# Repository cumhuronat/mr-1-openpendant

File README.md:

# mr-1-openpendant
An opensource pendant project for MR-1 CNC

## Overview
This project implements an open-source pendant system for the MR-1 CNC machine, providing a user-friendly interface for machine control and monitoring.
The system consists of two main components and detailed documentation for them can be found within their respective submodules.

### Pendant
- Custom-designed handheld controller
- Features a display interface for machine status and control
- Built using ESP32-based hardware
- Includes software implementation for the user interface and control logic

### Dongle
- USB interface for CNC machine communication
- Components:
  - PCB design files
  - 3D-printable enclosure
  - Arduino-based firmware using TinyUSB
  - Interface software

## Project Structure
- `/pendant` - Main pendant implementation
  - `/software` - Pendant firmware and interface code
- `/dongle` - USB interface dongle
  - `/enclosure` - 3D design files for the dongle case
  - `/pcb` - PCB design files
  - `/software` - Interface software

## Development Status
This project is currently under active development as part of the IMGD 5100 course final project.

## Acknowledgments
Special thanks to [Charlie Roberts](https://github.com/charlieroberts) for allowing this project to be developed as part of the IMGD 5100 final project.

## License
This project is open source and available under the[MIT License](https://opensource.org/licenses/MIT).

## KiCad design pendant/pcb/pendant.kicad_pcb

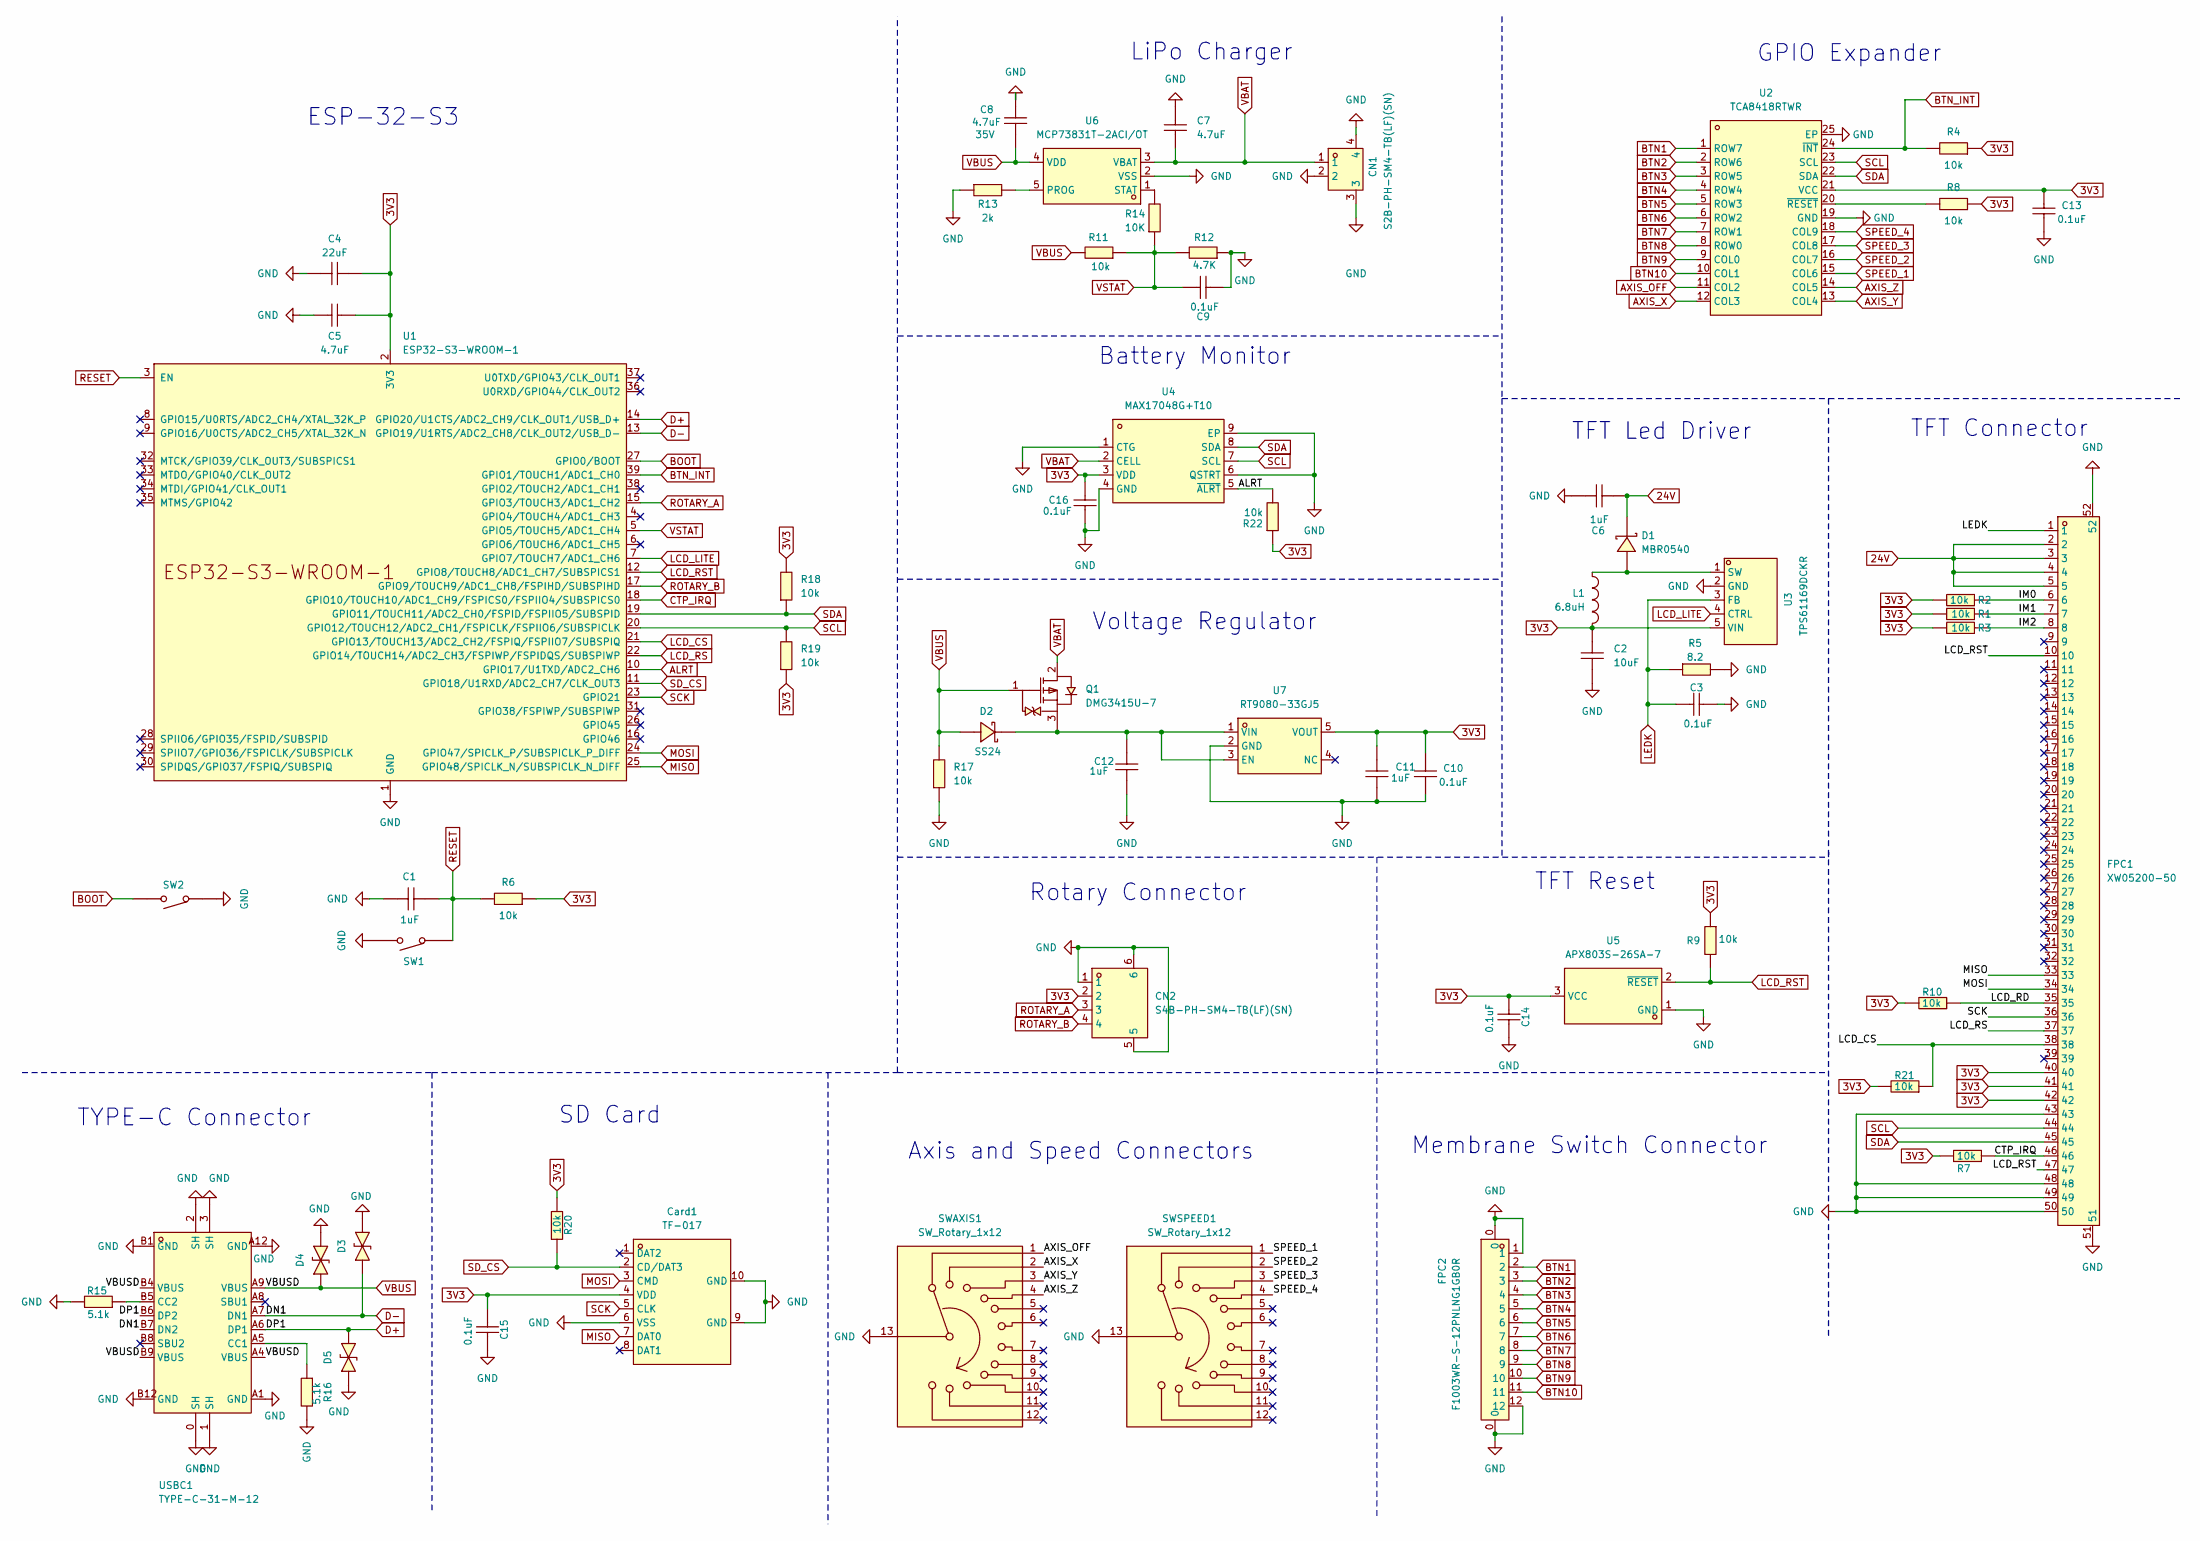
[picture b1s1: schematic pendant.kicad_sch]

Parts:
C1, C6, C11, C12: 1uF; C0402; LCSC Part C52923
C2: 10uF; C0805; LCSC Part C15850
C3, C9, C10, C13, C14, C15, C16: 0.1uF; C0402; LCSC Part C1525
C4: 22uF; C0603; LCSC Part C59461
C5, C7: 4.7uF; C0402; LCSC Part C23733
C8: 4.7uF; C0805; Voltage 35V; LCSC Part C668361
CN1: S2B-PH-SM4-TB(LF)(SN); CONN-SMD_P2.00_S2B-PH-SM4-TB-LF-SN; LCSC Part C295747
CN2: S4B-PH-SM4-TB(LF)(SN); CONN-SMD_S4B-PH-SM4-TB-LF-SN; LCSC Part C265102
Card1: TF-017; TF-SMD_TF-017; LCSC Part C410348
D1: MBR0540; SOD-123FL_L2.7-W1.8-LS3.8-RD; LCSC Part C116159
D2: SS24; SMA_L4.4-W2.8-LS5.4-R-RD; LCSC Part C489139
D3, D4, D5: LESD5D5.0CT1G; SOD-523_L1.2-W0.8-LS1.6-BI; LCSC Part C5246195
FPC1: XW05200-50; FPC-SMD_50P-P0.50_XW05200-50; LCSC Part C376073
FPC2: F1003WR-S-12PNLNG1GB0R; FPC-SMD_12P-P1.00_L5.5-W19.0; LCSC Part C247808
L1: 6.8uH; IND-SMD_L6.0-W6.0_SWPA6045S; LCSC Part C57254
Q1: DMG3415U-7; SOT-23-3_L2.9-W1.6-P1.90-LS2.8-BR-CW; LCSC Part C96616
R1, R2, R3, R4, R6, R7, R8, R9, R10, R11, R17, R18, R19, R20, R21, R22: 10k; R0402; LCSC Part C25744
R5: 8.2; R0402; LCSC Part C203098
R12: 4.7K; R0402; LCSC Part C140158
R13: 2k; R0402; LCSC Part C4109
R14: 10K; R0402; LCSC Part C25744
R15, R16: 5.1k; R0402; LCSC Part C25905
SW1, SW2: TS-1088-AR02016; SW-SMD_L3.9-W3.0-P4.45; LCSC Part C720477
SWAXIS1: SW_Rotary_1x12; CPA_12
SWSPEED1: SW_Rotary_1x12; CPA_12
U1: ESP32-S3-WROOM-1
U2: TCA8418RTWR; WQFN-24_L4.0-W4.0-P0.50-TL-EP2.5; LCSC Part C138713
U3: TPS61169DCKR; SC-70-5_L2.1-W1.3-P0.65-LS2.1-BR; LCSC Part C71045
U4: MAX17048G+T10; DFN-8_L2.0-W2.0-P0.50-BL-EP; LCSC Part C2682616
U5: APX803S-26SA-7; SOT-23-3_L2.9-W1.3-P1.83-LS2.4-BR; LCSC Part C526393
U6: MCP73831T-2ACI/OT; SOT-23-5_L3.0-W1.7-P0.95-LS2.8-BL; LCSC Part C424093
U7: RT9080-33GJ5; TSOT-23-5_L2.9-W1.6-P0.95-LS2.8-BL; LCSC Part C841192
USBC1: TYPE-C-31-M-12; USB-C_SMD-TYPE-C-31-M-12; LCSC Part C165948

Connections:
3V3: C2.2, C4.2, C5.2, C10.2, C11.1, C13.2, C14.1, C15.1, C16.1, CN2.2, Card1.4 (VDD), FPC1.40, FPC1.41, FPC1.42, L1.2, R1.2, R2.2, R3.2, R4.1, R6.1, R7.2, R8.1, R9.1, R10.2, R18.2, R19.1, R20.2, R21.2, R22.1, U1.2 (3V3), U2.21 (VCC), U3.5 (VIN), U4.3 (VDD), U5.3 (VCC), U7.5 (VOUT)
24V: C6.2, D1.1 (K), FPC1.2, FPC1.3, FPC1.4, FPC1.5
/IM0: FPC1.6, R2.1
/IM1: FPC1.7, R1.1
/IM2: FPC1.8, R3.1
/LCD_RD: FPC1.35, R10.1
ALRT: R22.2, U1.10 (GPIO17/U1TXD/ADC2_CH6), U4.5 (~ALRT)
AXIS_OFF: SWAXIS1.1, U2.11 (COL2)
AXIS_X: SWAXIS1.2, U2.12 (COL3)
AXIS_Y: SWAXIS1.3, U2.13 (COL4)
AXIS_Z: SWAXIS1.4, U2.14 (COL5)
BOOT: SW2.2, U1.27 (GPIO0/BOOT)
BTN1: FPC2.2, U2.1 (ROW7)
BTN2: FPC2.3, U2.2 (ROW6)
BTN3: FPC2.4, U2.3 (ROW5)
BTN4: FPC2.5, U2.4 (ROW4)
BTN5: FPC2.6, U2.5 (ROW3)
BTN6: FPC2.7, U2.6 (ROW2)
BTN7: FPC2.8, U2.7 (ROW1)
BTN8: FPC2.9, U2.8 (ROW0)
BTN9: FPC2.10, U2.9 (COL0)
BTN10: FPC2.11, U2.10 (COL1)
BTN_INT: R4.2, U1.39 (GPIO1/TOUCH1/ADC1_CH0), U2.24 (~INT)
CTP_IRQ: FPC1.46, R7.1, U1.18 (GPIO10/TOUCH10/ADC1_CH9/FSPICS0/FSPIIO4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)
D+: D5.1, U1.14 (GPIO20/U1CTS/ADC2_CH9/CLK_OUT1/USB_D+), USBC1.A6 (DP1), USBC1.B6 (DP2)
D-: D3.2, U1.13 (GPIO19/U1RTS/ADC2_CH8/CLK_OUT2/USB_D-), USBC1.A7 (DN1), USBC1.B7 (DN2)
GND: C1.2, C2.1, C3.2, C4.1, C5.1, C6.1, C7.2, C8.1, C9.2, C10.1, C11.2, C12.2, C13.1, C14.2, C15.2, C16.2, CN1.2, CN1.3, CN1.4, CN2.1, CN2.5, CN2.6, Card1.6 (VSS), Card1.9 (GND), Card1.10 (GND), D3.1, D4.1, D5.2, FPC1.43, FPC1.48, FPC1.49, FPC1.50, FPC1.51, FPC1.52, FPC2.0, FPC2.1, FPC2.12, R5.2, R12.1, R13.1, R15.2, R16.2, R17.1, SW1.2, SW2.1, SWAXIS1.13, SWSPEED1.13, U1.1 (GND), U1.40 (GND), U1.41 (GND), U2.19 (GND), U2.25 (EP), U3.2 (GND), U4.1 (CTG), U4.4 (GND), U4.6 (QSTRT), U4.9 (EP), U5.1 (GND), U6.2 (VSS), U7.2 (GND), USBC1.0 (SH), USBC1.1 (SH), USBC1.2 (SH), USBC1.3 (SH), USBC1.A1 (GND), USBC1.A12 (GND), USBC1.B1 (GND), USBC1.B12 (GND)
LCD_CS: FPC1.38, R21.1, U1.21 (GPIO13/TOUCH13/ADC2_CH2/FSPIQ/FSPIIO7/S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)
LCD_LITE: U1.7 (GPIO7/TOUCH7/ADC1_CH6), U3.4 (CTRL)
LCD_RS: FPC1.37, U1.22 (GPIO14/TOUCH14/ADC2_CH3/FSPIWP/FSPIDQS/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)
LCD_RST: FPC1.10, FPC1.47, R9.2, U1.12 (GPIO8/TOUCH8/ADC1_CH7/SUBSPICS1), U5.2 (~RESET)
LEDK: C3.1, FPC1.1, R5.1, U3.3 (FB)
MISO: Card1.7 (DAT0), FPC1.33, U1.25 (GPIO48/SPICLK_N/SUBSPICLK_N_DIFF)
MOSI: Card1.3 (CMD), FPC1.34, U1.24 (GPIO47/SPICLK_P/SUBSPICLK_P_DIFF)
unnamed: D1.2 (A), L1.1, U3.1 (SW)
unnamed: C12.1, D2.2 (K), Q1.3 (S), U7.1 (VIN), U7.3 (EN)
unnamed: R8.2, U2.20 (~RESET)
unnamed: R13.2, U6.5 (PROG)
unnamed: R14.2, U6.1 (STAT)
unnamed: R16.1, USBC1.A5 (CC1)
unnamed: R15.1, USBC1.B5 (CC2)
RESET: C1.1, R6.2, SW1.1, U1.3 (EN)
ROTARY_A: CN2.3, U1.15 (GPIO3/TOUCH3/ADC1_CH2)
ROTARY_B: CN2.4, U1.17 (GPIO9/TOUCH9/ADC1_CH8/FSPIHD/SUBSPIHD)
SCK: Card1.5 (CLK), FPC1.36, U1.23 (GPIO21)
SCL: FPC1.44, R19.2, U1.20 (GPIO12/TOUCH12/ADC2_CH1/FSPICLK/FSPIIO6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), U2.23 (SCL), U4.7 (SCL)
SDA: FPC1.45, R18.1, U1.19 (GPIO11/TOUCH11/ADC2_CH0/FSPID/FSPIIO5/S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), U2.22 (SDA), U4.8 (SDA)
SD_CS: Card1.2 (CD/DAT3), R20.1, U1.11 (GPIO18/U1RXD/ADC2_CH7/CLK_OUT3)
SPEED_1: SWSPEED1.1, U2.15 (COL6)
SPEED_2: SWSPEED1.2, U2.16 (COL7)
SPEED_3: SWSPEED1.3, U2.17 (COL8)
SPEED_4: SWSPEED1.4, U2.18 (COL9)
VBAT: C7.1, CN1.1, Q1.2 (D), U4.2 (CELL), U6.3 (VBAT)
VBUS: C8.2, D2.1 (A), D4.2, Q1.1 (G), R11.2, R17.2, U6.4 (VDD), USBC1.A4 (VBUS), USBC1.A9 (VBUS), USBC1.B4 (VBUS), USBC1.B9 (VBUS)
VSTAT: C9.1, R11.1, R12.2, R14.1, U1.5 (GPIO5/TOUCH5/ADC1_CH4)

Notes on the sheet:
Axis and Speed Connectors
ESP-32-S3
Rotary Connector
Battery Monitor
TFT Reset
SD Card
Membrane Switch Connector
LiPo Charger
TYPE-C Connector
GPIO Expander
Voltage Regulator
TFT Connector
TFT Led Driver

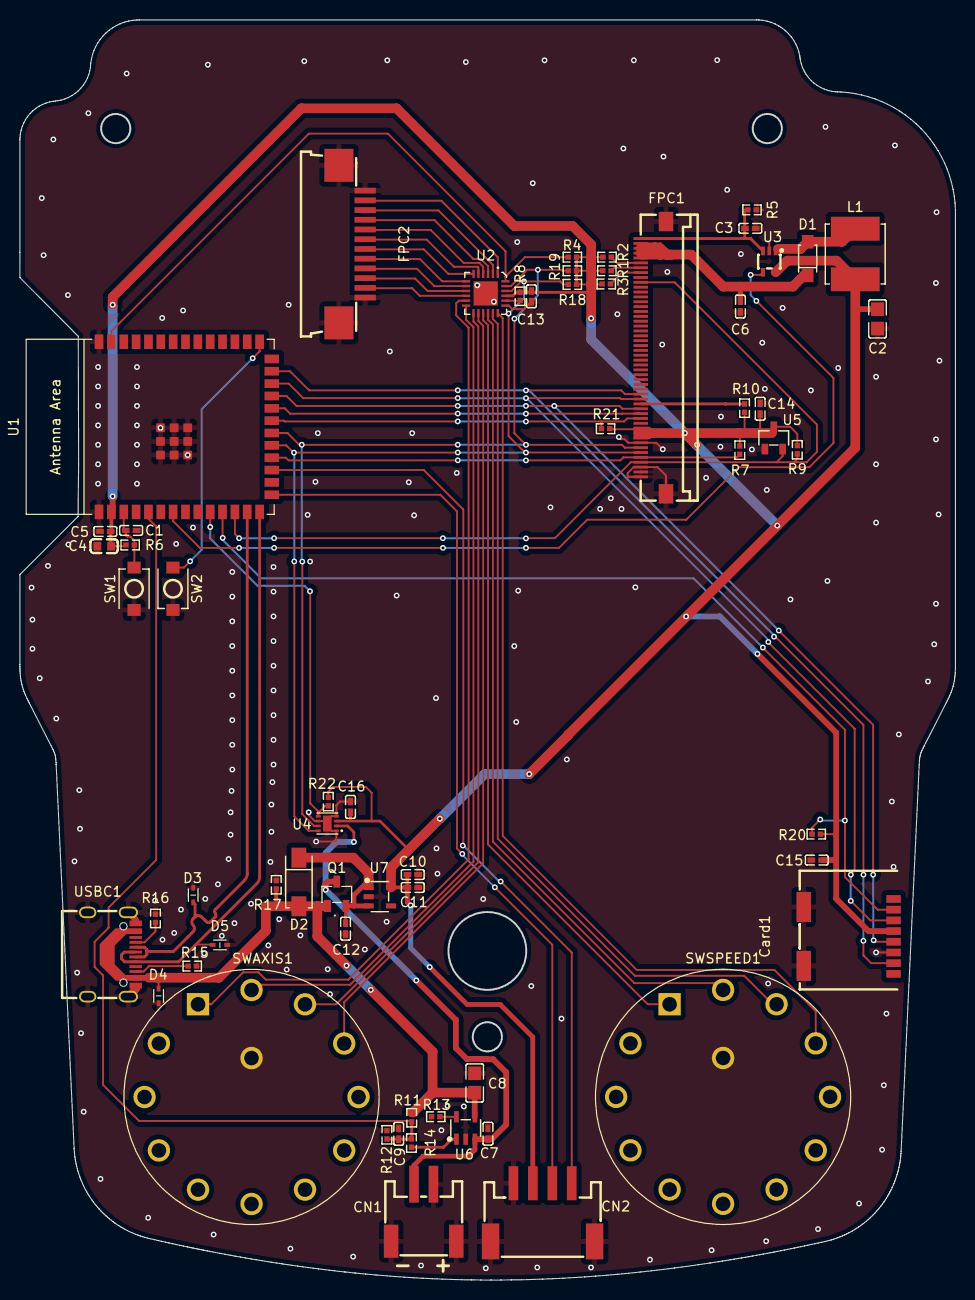
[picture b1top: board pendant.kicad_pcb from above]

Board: 2 copper layers, 96.1 x 129.5 mm, 62 parts (0 on the bottom side), 55 nets.

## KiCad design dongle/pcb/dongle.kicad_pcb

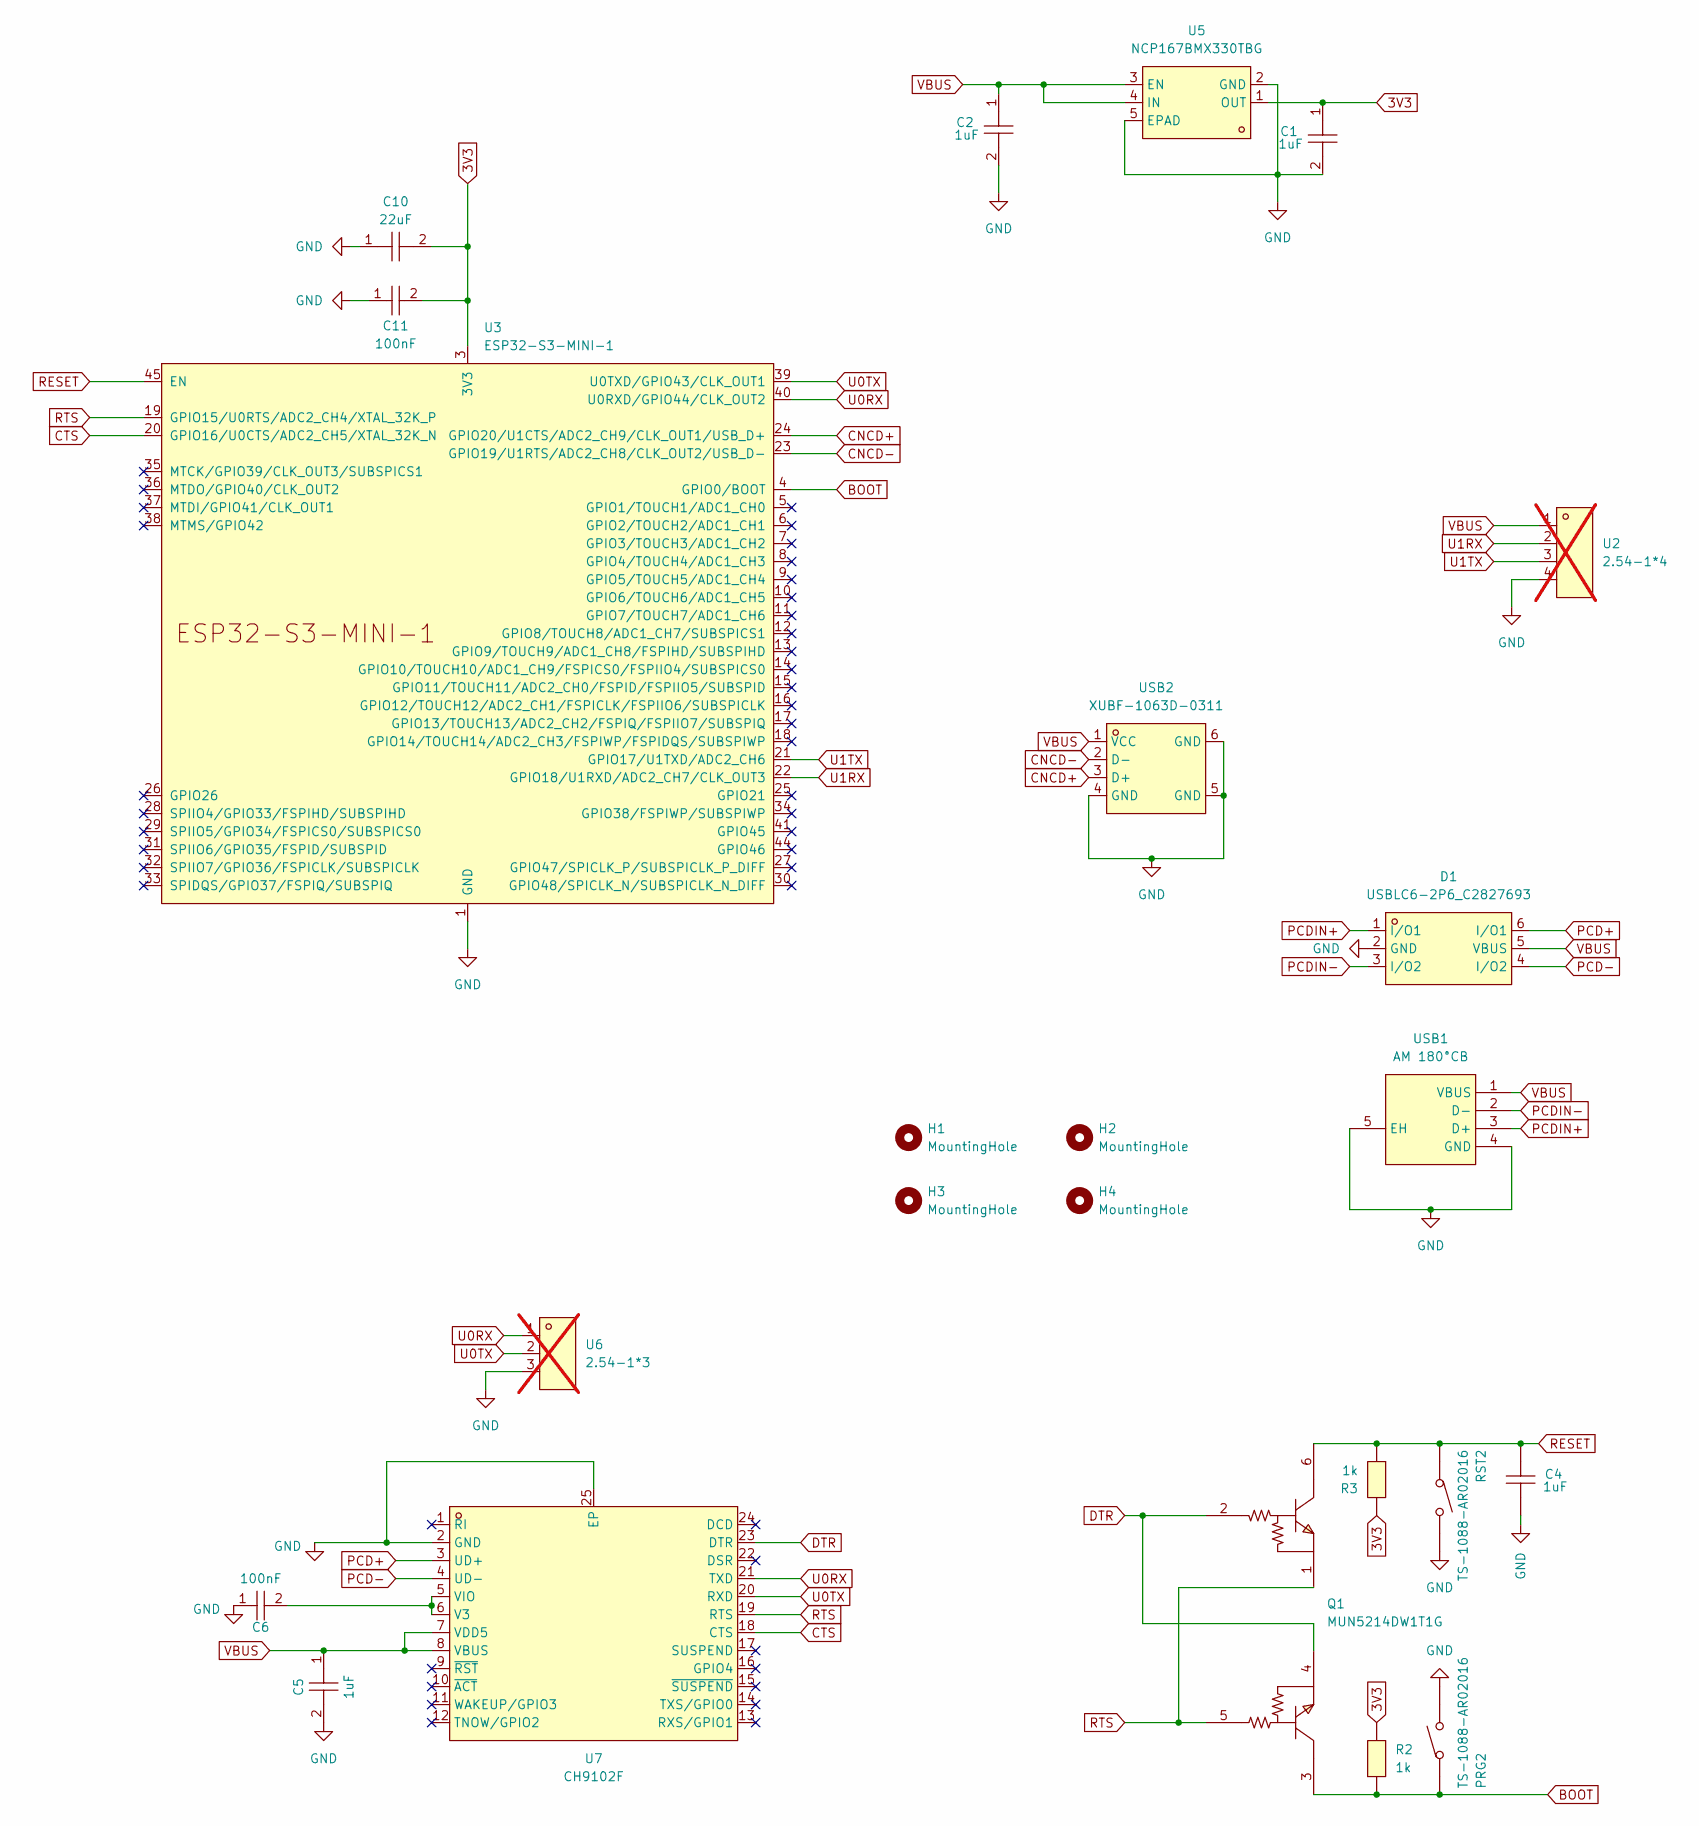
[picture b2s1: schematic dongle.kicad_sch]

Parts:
C1, C2, C4, C5: 1uF; C0402; LCSC Part C52923
C6, C11: 100nF; C0402; LCSC Part C1525
C10: 22uF; C0603; LCSC Part C59461
D1: USBLC6-2P6_C2827693; SOT-666-6_L1.6-W1.2-P0.50-LS1.6-BL; LCSC Part C2827693
H1, H2, H3, H4: MountingHole; MountingHole_2.2mm_M2_DIN965
PRG2: TS-1088-AR02016; SW-SMD_L3.9-W3.0-P4.45; LCSC Part C720477
Q1: MUN5214DW1T1G; SOT-363_L2.0-W1.3-P0.65-LS2.1-TL; LCSC Part C94403
R2, R3: 1k; R0201; LCSC Part C490807
RST2: TS-1088-AR02016; SW-SMD_L3.9-W3.0-P4.45; LCSC Part C720477
U2: 2.54-1*4; HDR-TH_4P-P2.54-V-M-1; LCSC Part C5116483; not fitted
U3: ESP32-S3-MINI-1
U5: NCP167BMX330TBG; onsemi-711AJ-03_2022-C-MFG; LCSC Part C892227
U6: 2.54-1*3; HDR-TH_3P-P2.54-V-M-1; LCSC Part C5116483; not fitted
U7: CH9102F; QFN-24_L4.0-W4.0-P0.50-BL-EP2.5; LCSC Part C2858418
USB1: AM 180°CB; USB-SMD_AM180CB; LCSC Part C2681565
USB2: XUBF-1063D-0311; USB-A-TH_XUBF-1063D-0311; LCSC Part C7527653

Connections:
3V3: C1.1, C10.2, C11.2, R2.2, R3.2, U3.3 (3V3), U5.1 (OUT)
BOOT: PRG2.1, Q1.3, R2.1, U3.4 (GPIO0/BOOT)
CNCD+: U3.24 (GPIO20/U1CTS/ADC2_CH9/CLK_OUT1/USB_D+), USB2.3 (D+)
CNCD-: U3.23 (GPIO19/U1RTS/ADC2_CH8/CLK_OUT2/USB_D-), USB2.2 (D-)
CTS: U3.20 (GPIO16/U0CTS/ADC2_CH5/XTAL_32K_N), U7.18 (CTS)
DTR: Q1.2, Q1.4, U7.23 (DTR)
GND: C1.2, C2.2, C4.2, C5.2, C6.1, C10.1, C11.1, D1.2 (GND), PRG2.2, RST2.2, U2.4, U3.1 (GND), U3.2 (GND), U3.42 (GND), U3.43 (GND), U3.46 (GND), U3.47 (GND), U3.48 (GND), U3.49 (GND), U3.50 (GND), U3.51 (GND), U3.52 (GND), U3.53 (GND), U3.54 (GND), U3.55 (GND), U3.56 (GND), U3.57 (GND), U3.58 (GND), U3.59 (GND), U3.60 (GND), U3.61 (GND), U3.62 (GND), U3.63 (GND), U3.64 (GND), U3.65 (GND), U5.2 (GND), U5.5 (EPAD), U6.3, U7.2 (GND), U7.25 (EP), USB1.4 (GND), USB1.5 (EH), USB2.4 (GND), USB2.5 (GND), USB2.6 (GND)
unnamed: C6.2, U7.5 (VIO), U7.6 (V3)
PCD+: D1.6 (I/O1), U7.3 (UD+)
PCD-: D1.4 (I/O2), U7.4 (UD-)
PCDIN+: D1.1 (I/O1), USB1.3 (D+)
PCDIN-: D1.3 (I/O2), USB1.2 (D-)
RESET: C4.1, Q1.6, R3.1, RST2.1, U3.45 (EN)
RTS: Q1.1, Q1.5, U3.19 (GPIO15/U0RTS/ADC2_CH4/XTAL_32K_P), U7.19 (RTS)
U0RX: U3.40 (U0RXD/GPIO44/CLK_OUT2), U6.1, U7.21 (TXD)
U0TX: U3.39 (U0TXD/GPIO43/CLK_OUT1), U6.2, U7.20 (RXD)
U1RX: U2.2, U3.22 (GPIO18/U1RXD/ADC2_CH7/CLK_OUT3)
U1TX: U2.3, U3.21 (GPIO17/U1TXD/ADC2_CH6)
VBUS: C2.1, C5.1, D1.5 (VBUS), U2.1, U5.3 (EN), U5.4 (IN), U7.7 (VDD5), U7.8 (VBUS), USB1.1 (VBUS), USB2.1 (VCC)

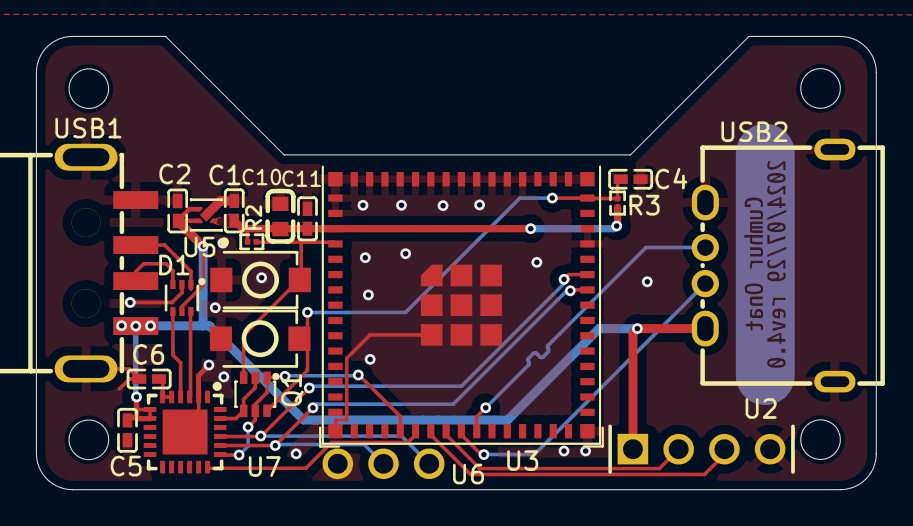
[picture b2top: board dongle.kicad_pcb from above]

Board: 2 copper layers, 46.7 x 25.2 mm, 25 parts (1 on the bottom side), 19 nets.

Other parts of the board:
kibuzzard-66A861F5: G***; kibuzzard-66A861F5

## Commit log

2024-06-30 initial test for serial bridge
2024-06-30 add ota support
2024-07-01 fix race conditions in threads
2024-07-01 working version before refactor
2024-07-01 code refactor
2024-07-01 kicad project for the dongle
2024-07-02 grbl status parser wip
2024-07-03 separate ble characteristics for each variable
2024-07-04 enclosure
2024-07-04 pcb for pendant
2024-07-09 fix errors on pendant pcb
2024-07-31 use ch9102f for pc usb
2024-07-31 add dongle software as submoldue
2024-11-21 update pendant pcb
2024-11-21 remove empty software folder
2024-11-21 add pendant firmware as submodule
2024-11-21 add fusion project for pendant enclosure
2024-11-21 update dongle firmware
2024-12-08 new enclosure
2024-12-08 images
2024-12-08 add images to readme
